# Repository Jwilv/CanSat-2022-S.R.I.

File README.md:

# CanSat-2022-S.R.I.
GRUPO S.R.I

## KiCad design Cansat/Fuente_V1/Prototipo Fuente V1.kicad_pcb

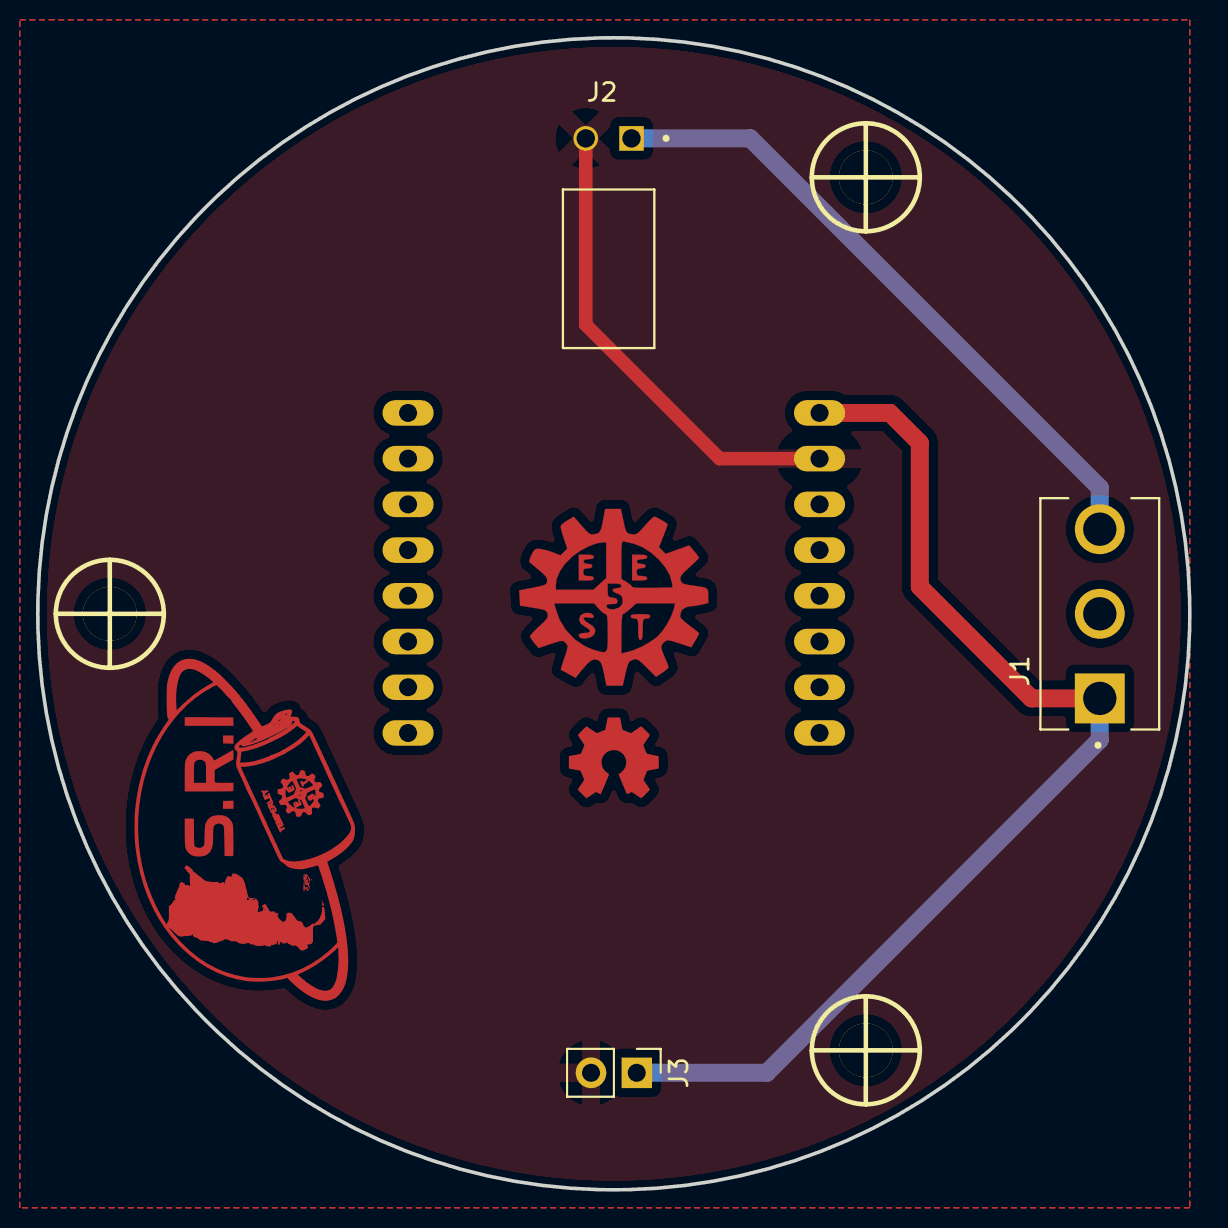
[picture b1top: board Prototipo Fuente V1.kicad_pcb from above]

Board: 2 copper layers, 64.0 x 64.0 mm, 8 parts (1 on the bottom side), 2 nets.

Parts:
ESP32-CAM1: ESP32-CAM
H1, H2, H3: Mounting_Hole; hole_3mm
H6: Mounting_Hole; Logo_OSHW_6x6mm_FCu
J1: SWITCH PRINCIPAL; SW_500SSP1S2M2QEA
J2: conector bateria; TE_3-647630-2
J3: alimentacion placa superior; PinHeader_1x02_P2.54mm_Vertical

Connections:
+5V: ESP32-CAM1.P$1 (5V), J1.1, J1.3, J2.1, J3.1
GND: ESP32-CAM1.P$2 (GND), J2.2, J3.2
